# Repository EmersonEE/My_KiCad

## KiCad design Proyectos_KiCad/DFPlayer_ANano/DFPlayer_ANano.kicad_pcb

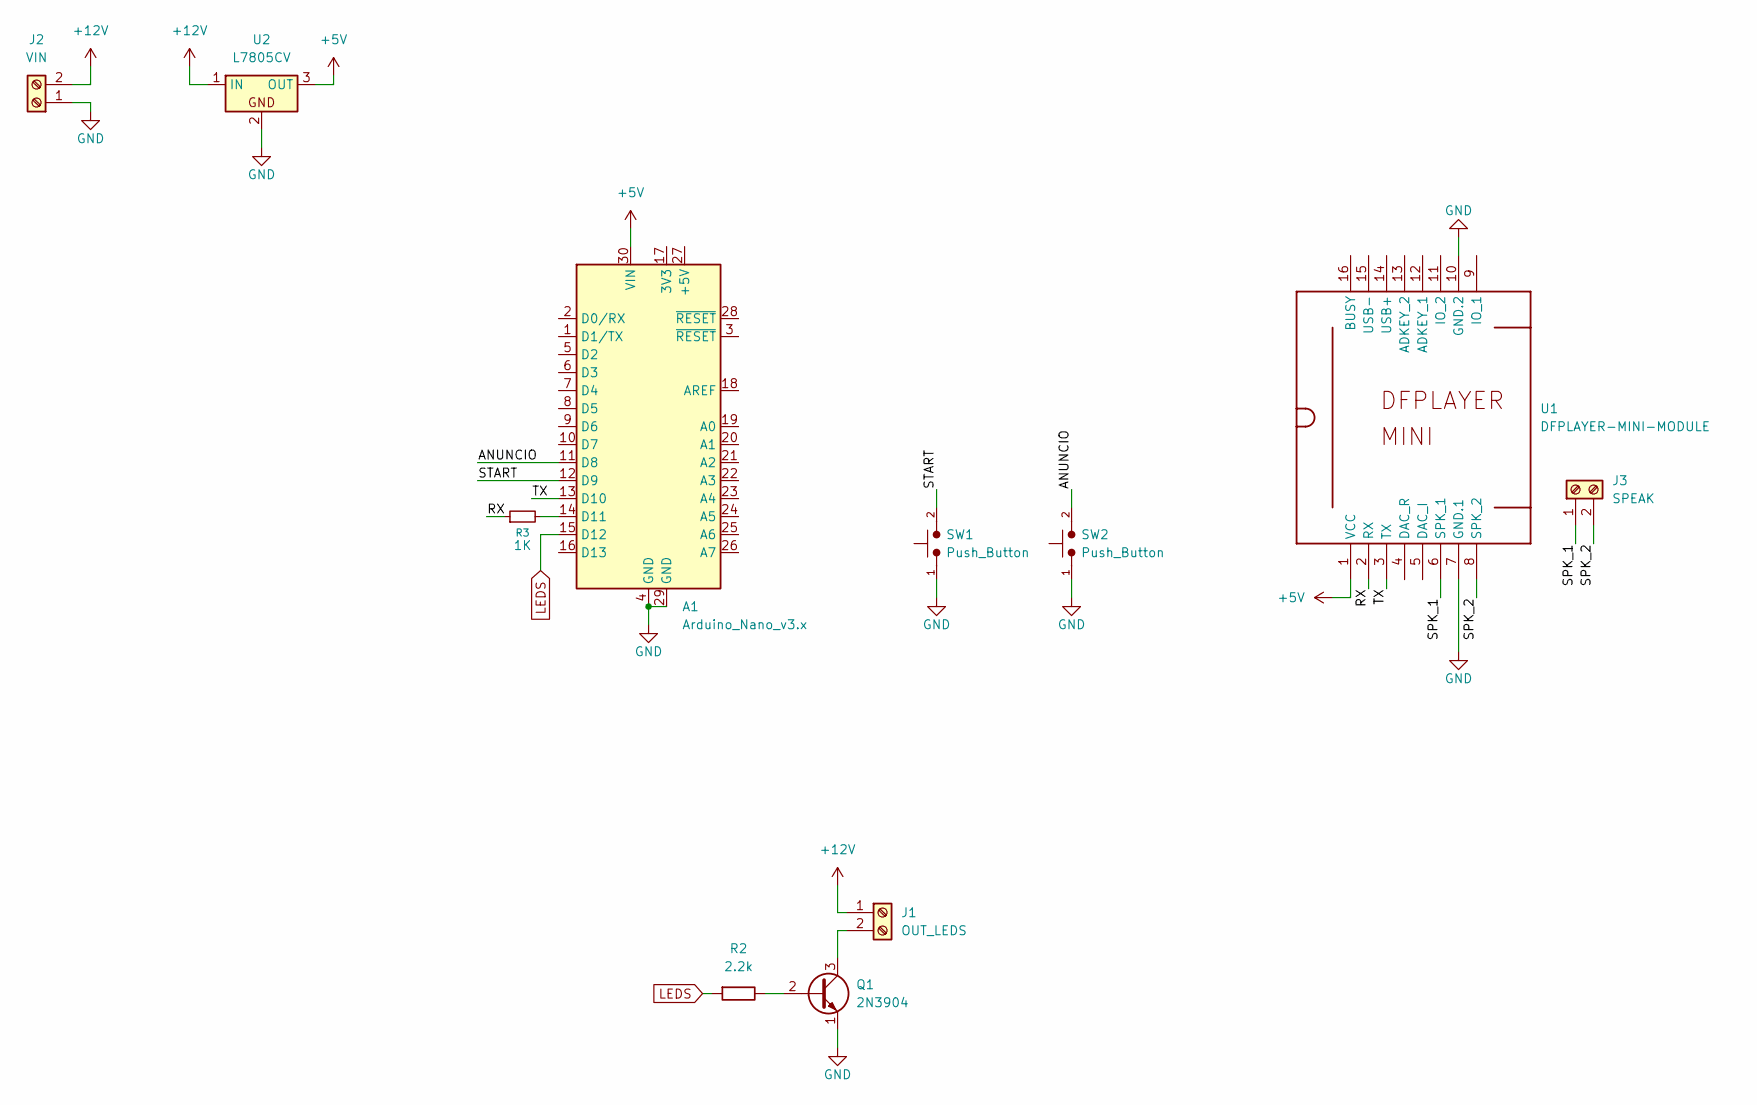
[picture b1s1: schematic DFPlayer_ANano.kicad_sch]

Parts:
A1: Arduino_Nano_v3.x; Arduino_Nano
J1: OUT_LEDS; TerminalBlock_Phoenix_MKDS-1,5-2-5.08_1x02_P5.08mm_Horizont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
J2: VIN; TerminalBlock_Phoenix_MKDS-1,5-2-5.08_1x02_P5.08mm_Horizont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
J3: SPEAK; TerminalBlock_Phoenix_MKDS-1,5-2-5.08_1x02_P5.08mm_Horizont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
Q1: 2N3904; TO-92L_Inline_Wide
R2: 2.2k; R_Axial_DIN0207_L6.3mm_D2.5mm_P10.16mm_Horizontal
R3: 1K; R_Axial_DIN0204_L3.6mm_D1.6mm_P10.16mm_Horizontal
SW1, SW2: Push_Button; SW_PUSH_6mm
U1: DFPLAYER-MINI-MODULE
U2: L7805CV; TO-220-3_Vertical

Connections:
+5V: A1.30 (VIN), U1.1 (VCC), U2.3 (OUT)
+12V: J1.1, J2.2, U2.1 (IN)
/ANUNCIO: A1.11 (D8), SW2.2
/RX: R3.1, U1.2 (RX)
/SPK_1: J3.1, U1.6 (SPK_1)
/SPK_2: J3.2, U1.8 (SPK_2)
/START: A1.12 (D9), SW1.2
/TX: A1.13 (D10), U1.3 (TX)
GND: A1.4 (GND), A1.29 (GND), J2.1, Q1.1 (E), SW1.1, SW2.1, U1.7 (GND.1), U1.10 (GND.2), U2.2
LEDS: A1.15 (D12), R2.1
unnamed: A1.14 (D11), R3.2
unnamed: J1.2, Q1.3 (C)
unnamed: Q1.2 (B), R2.2

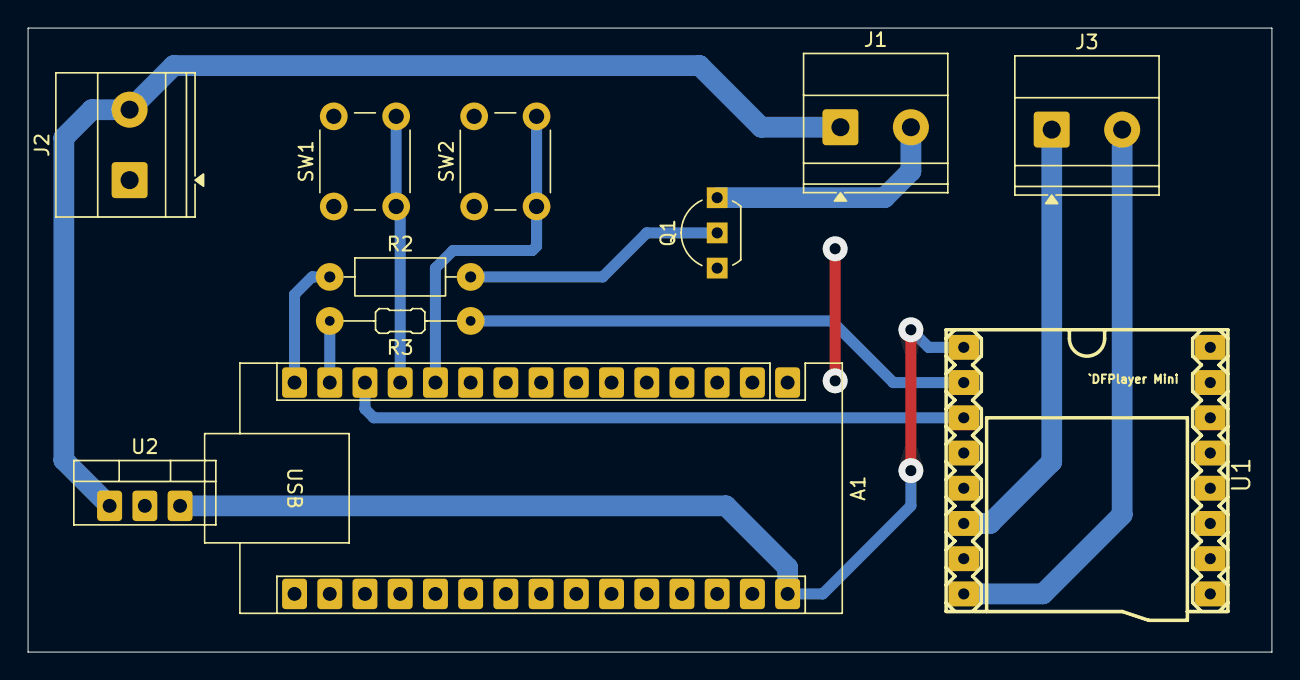
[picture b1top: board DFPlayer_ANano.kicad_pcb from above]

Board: 2 copper layers, 89.7 x 45.0 mm, 11 parts (0 on the bottom side), 13 nets.

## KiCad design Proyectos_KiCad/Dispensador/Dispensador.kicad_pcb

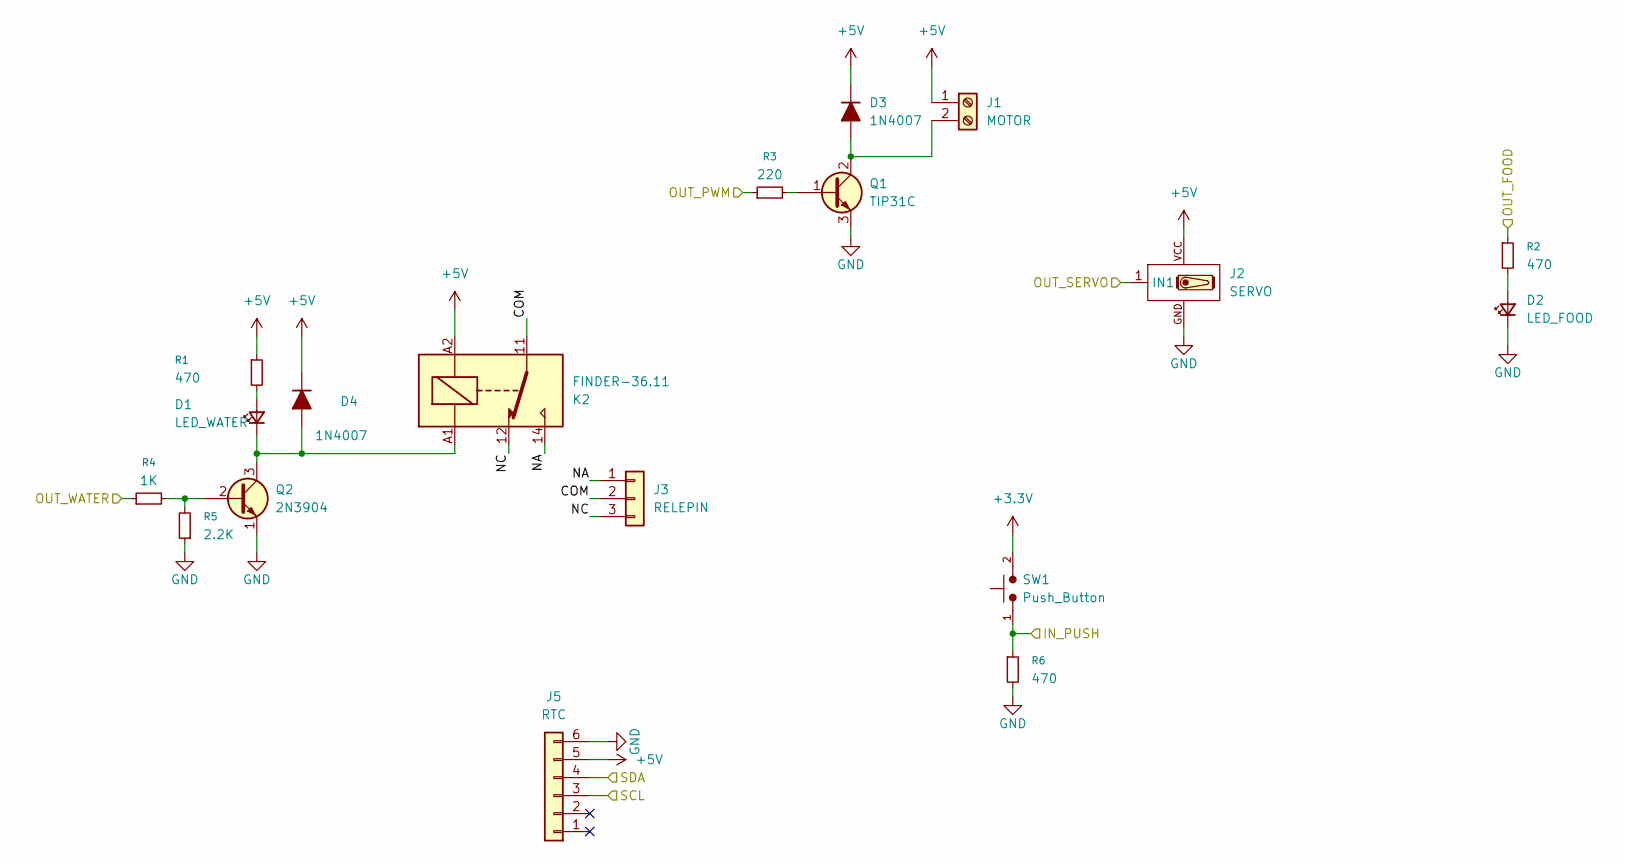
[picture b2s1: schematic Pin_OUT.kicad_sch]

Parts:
D1: LED_WATER; LED_D5.0mm
D2: LED_FOOD; LED_D5.0mm
D3, D4: 1N4007; D_DO-41_SOD81_P7.62mm_Horizontal
J1: MOTOR; TerminalBlock_Phoenix_MKDS-1,5-2-5.08_1x02_P5.08mm_Horizont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
J2: SERVO; ServoPort_01_Vertical
J3: RELEPIN; TerminalBlock_Phoenix_MKDS-1,5-3-5.08_1x03_P5.08mm_Horizont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
J5: RTC; PinSocket_1x06_P2.54mm_Vertical
K2: FINDER-36.11; Relay_SPDT_Finder_36.11
Q1: TIP31C; TO-220-3_Vertical_BCE
Q2: 2N3904; TO-92_Inline_Wide_EBC
R1, R2, R6: 470
R3: 220
R4: 1K
R5: 2.2K
SW1: Push_Button; SW_PUSH_6mm

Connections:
+3.3V: SW1.2; also elsewhere on the board
+5V: D3.1 (K), D4.1 (K), J1.1, J2.VCC, J5.5, K2.A2, R1.1; also elsewhere on the board
/ESP32/IN_PUSH: R6.1, SW1.1; also elsewhere on the board
/ESP32/OUT_FOOD: R2.1; also elsewhere on the board
/ESP32/OUT_PWM: R3.1; also elsewhere on the board
/ESP32/OUT_SERVO: J2.1 (IN1); also elsewhere on the board
/ESP32/OUT_WATER: R4.1; also elsewhere on the board
/ESP32/SCL: J5.3; also elsewhere on the board
/ESP32/SDA: J5.4; also elsewhere on the board
/Pin_OUT/COM: J3.2, K2.11
/Pin_OUT/NA: J3.1, K2.14
/Pin_OUT/NC: J3.3, K2.12
GND: D2.1 (K), J2.GND, J5.6, Q1.3 (E), Q2.1 (E), R5.1, R6.2; also elsewhere on the board
unnamed: D1.2 (A), R1.2
unnamed: D1.1 (K), D4.2 (A), K2.A1, Q2.3 (C)
unnamed: D2.2 (A), R2.2
unnamed: D3.2 (A), J1.2, Q1.2 (C)
unnamed: Q1.1 (B), R3.2
unnamed: Q2.2 (B), R4.2, R5.2

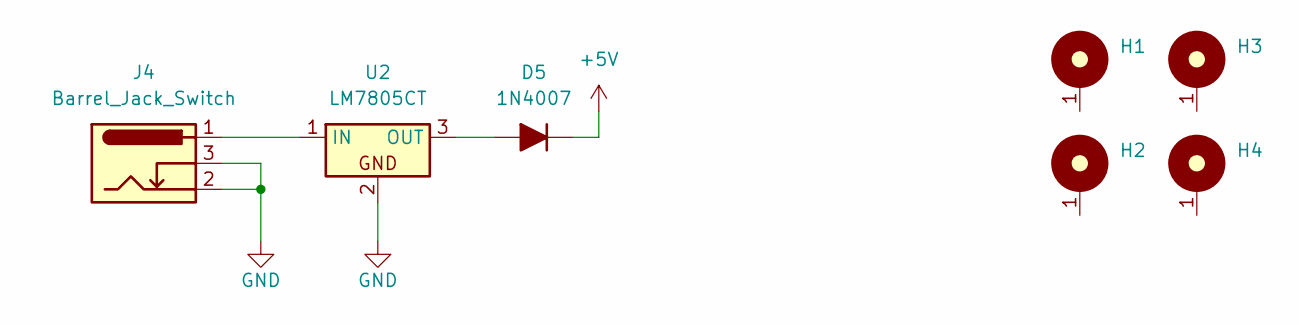
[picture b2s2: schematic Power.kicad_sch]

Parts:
D5: 1N4007; D_DO-41_SOD81_P7.62mm_Horizontal
H1, H2, H3, H4: MountingHole_3.2mm_M3_ISO14580
J4: Barrel_Jack_Switch; BarrelJack_Horizontal
U2: LM7805CT; TO-220-3_Vertical

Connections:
+5V: D5.1 (K); also elsewhere on the board
GND: J4.2, J4.3, U2.2; also elsewhere on the board
unnamed: D5.2 (A), U2.3 (OUT)
unnamed: J4.1, U2.1 (IN)

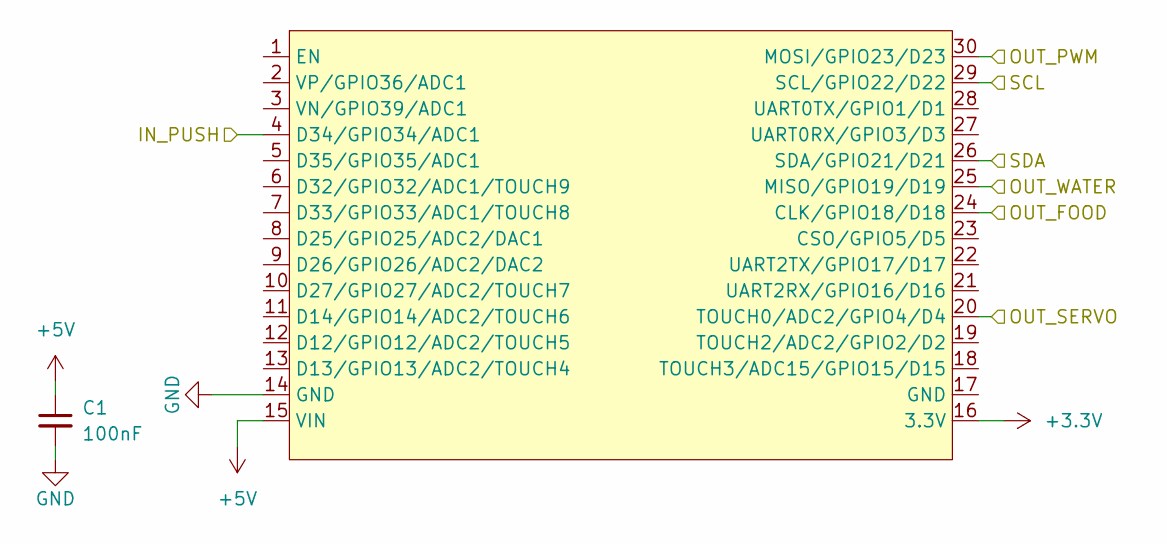
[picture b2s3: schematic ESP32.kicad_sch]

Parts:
C1: 100nF; C_Disc_D4.3mm_W1.9mm_P5.00mm
U1: ESP32_DevKit_V1_DOIT; ESP32_DEVKIT_V1_E32

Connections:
+3.3V: U1.16 (3.3V); also elsewhere on the board
+5V: C1.1, U1.15 (VIN); also elsewhere on the board
/ESP32/IN_PUSH: U1.4 (D34/GPIO34/ADC1); also elsewhere on the board
/ESP32/OUT_FOOD: U1.24 (CLK/GPIO18/D18); also elsewhere on the board
/ESP32/OUT_PWM: U1.30 (MOSI/GPIO23/D23); also elsewhere on the board
/ESP32/OUT_SERVO: U1.20 (TOUCH0/ADC2/GPIO4/D4); also elsewhere on the board
/ESP32/OUT_WATER: U1.25 (MISO/GPIO19/D19); also elsewhere on the board
/ESP32/SCL: U1.29 (SCL/GPIO22/D22); also elsewhere on the board
/ESP32/SDA: U1.26 (SDA/GPIO21/D21); also elsewhere on the board
GND: C1.2, U1.14 (GND); also elsewhere on the board

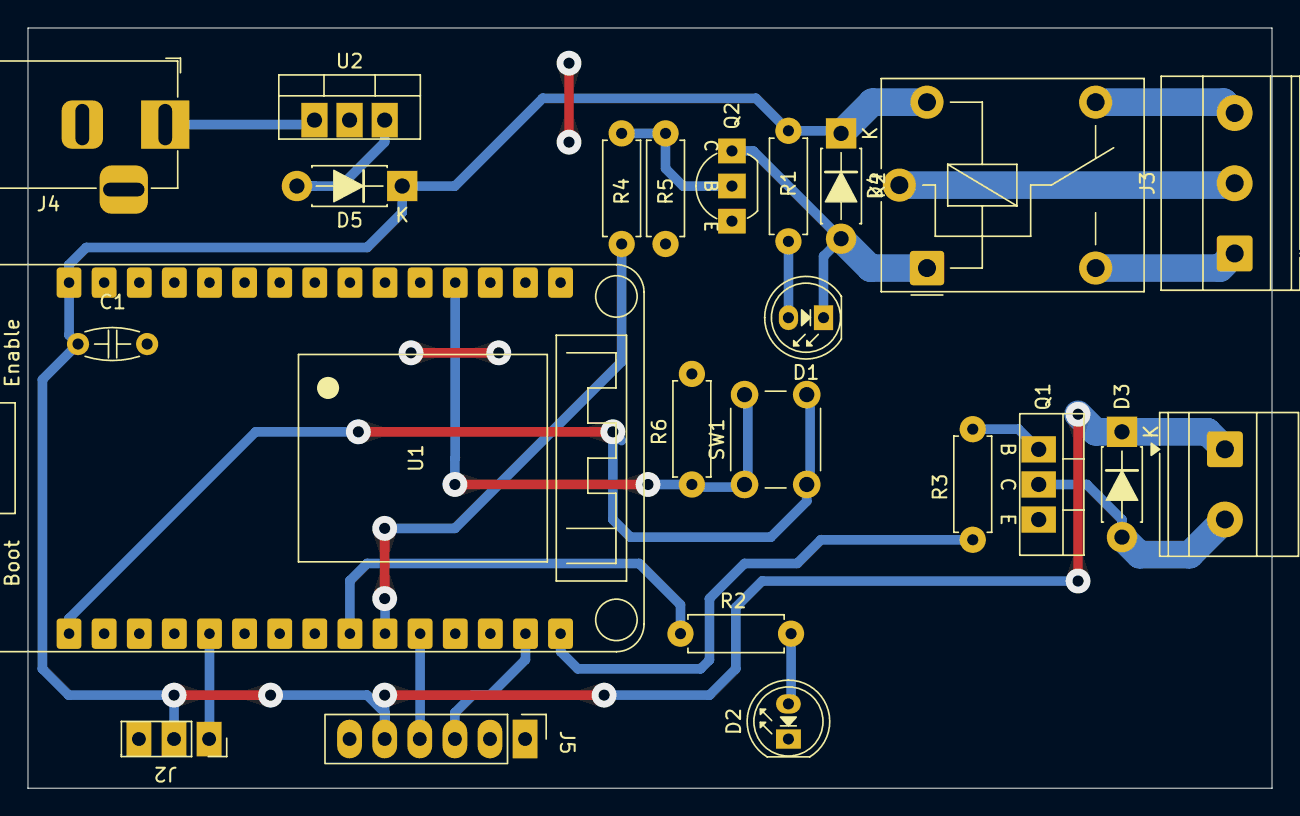
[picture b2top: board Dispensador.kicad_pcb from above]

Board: 2 copper layers, 90.0 x 55.0 mm, 27 parts (0 on the bottom side), 21 nets.

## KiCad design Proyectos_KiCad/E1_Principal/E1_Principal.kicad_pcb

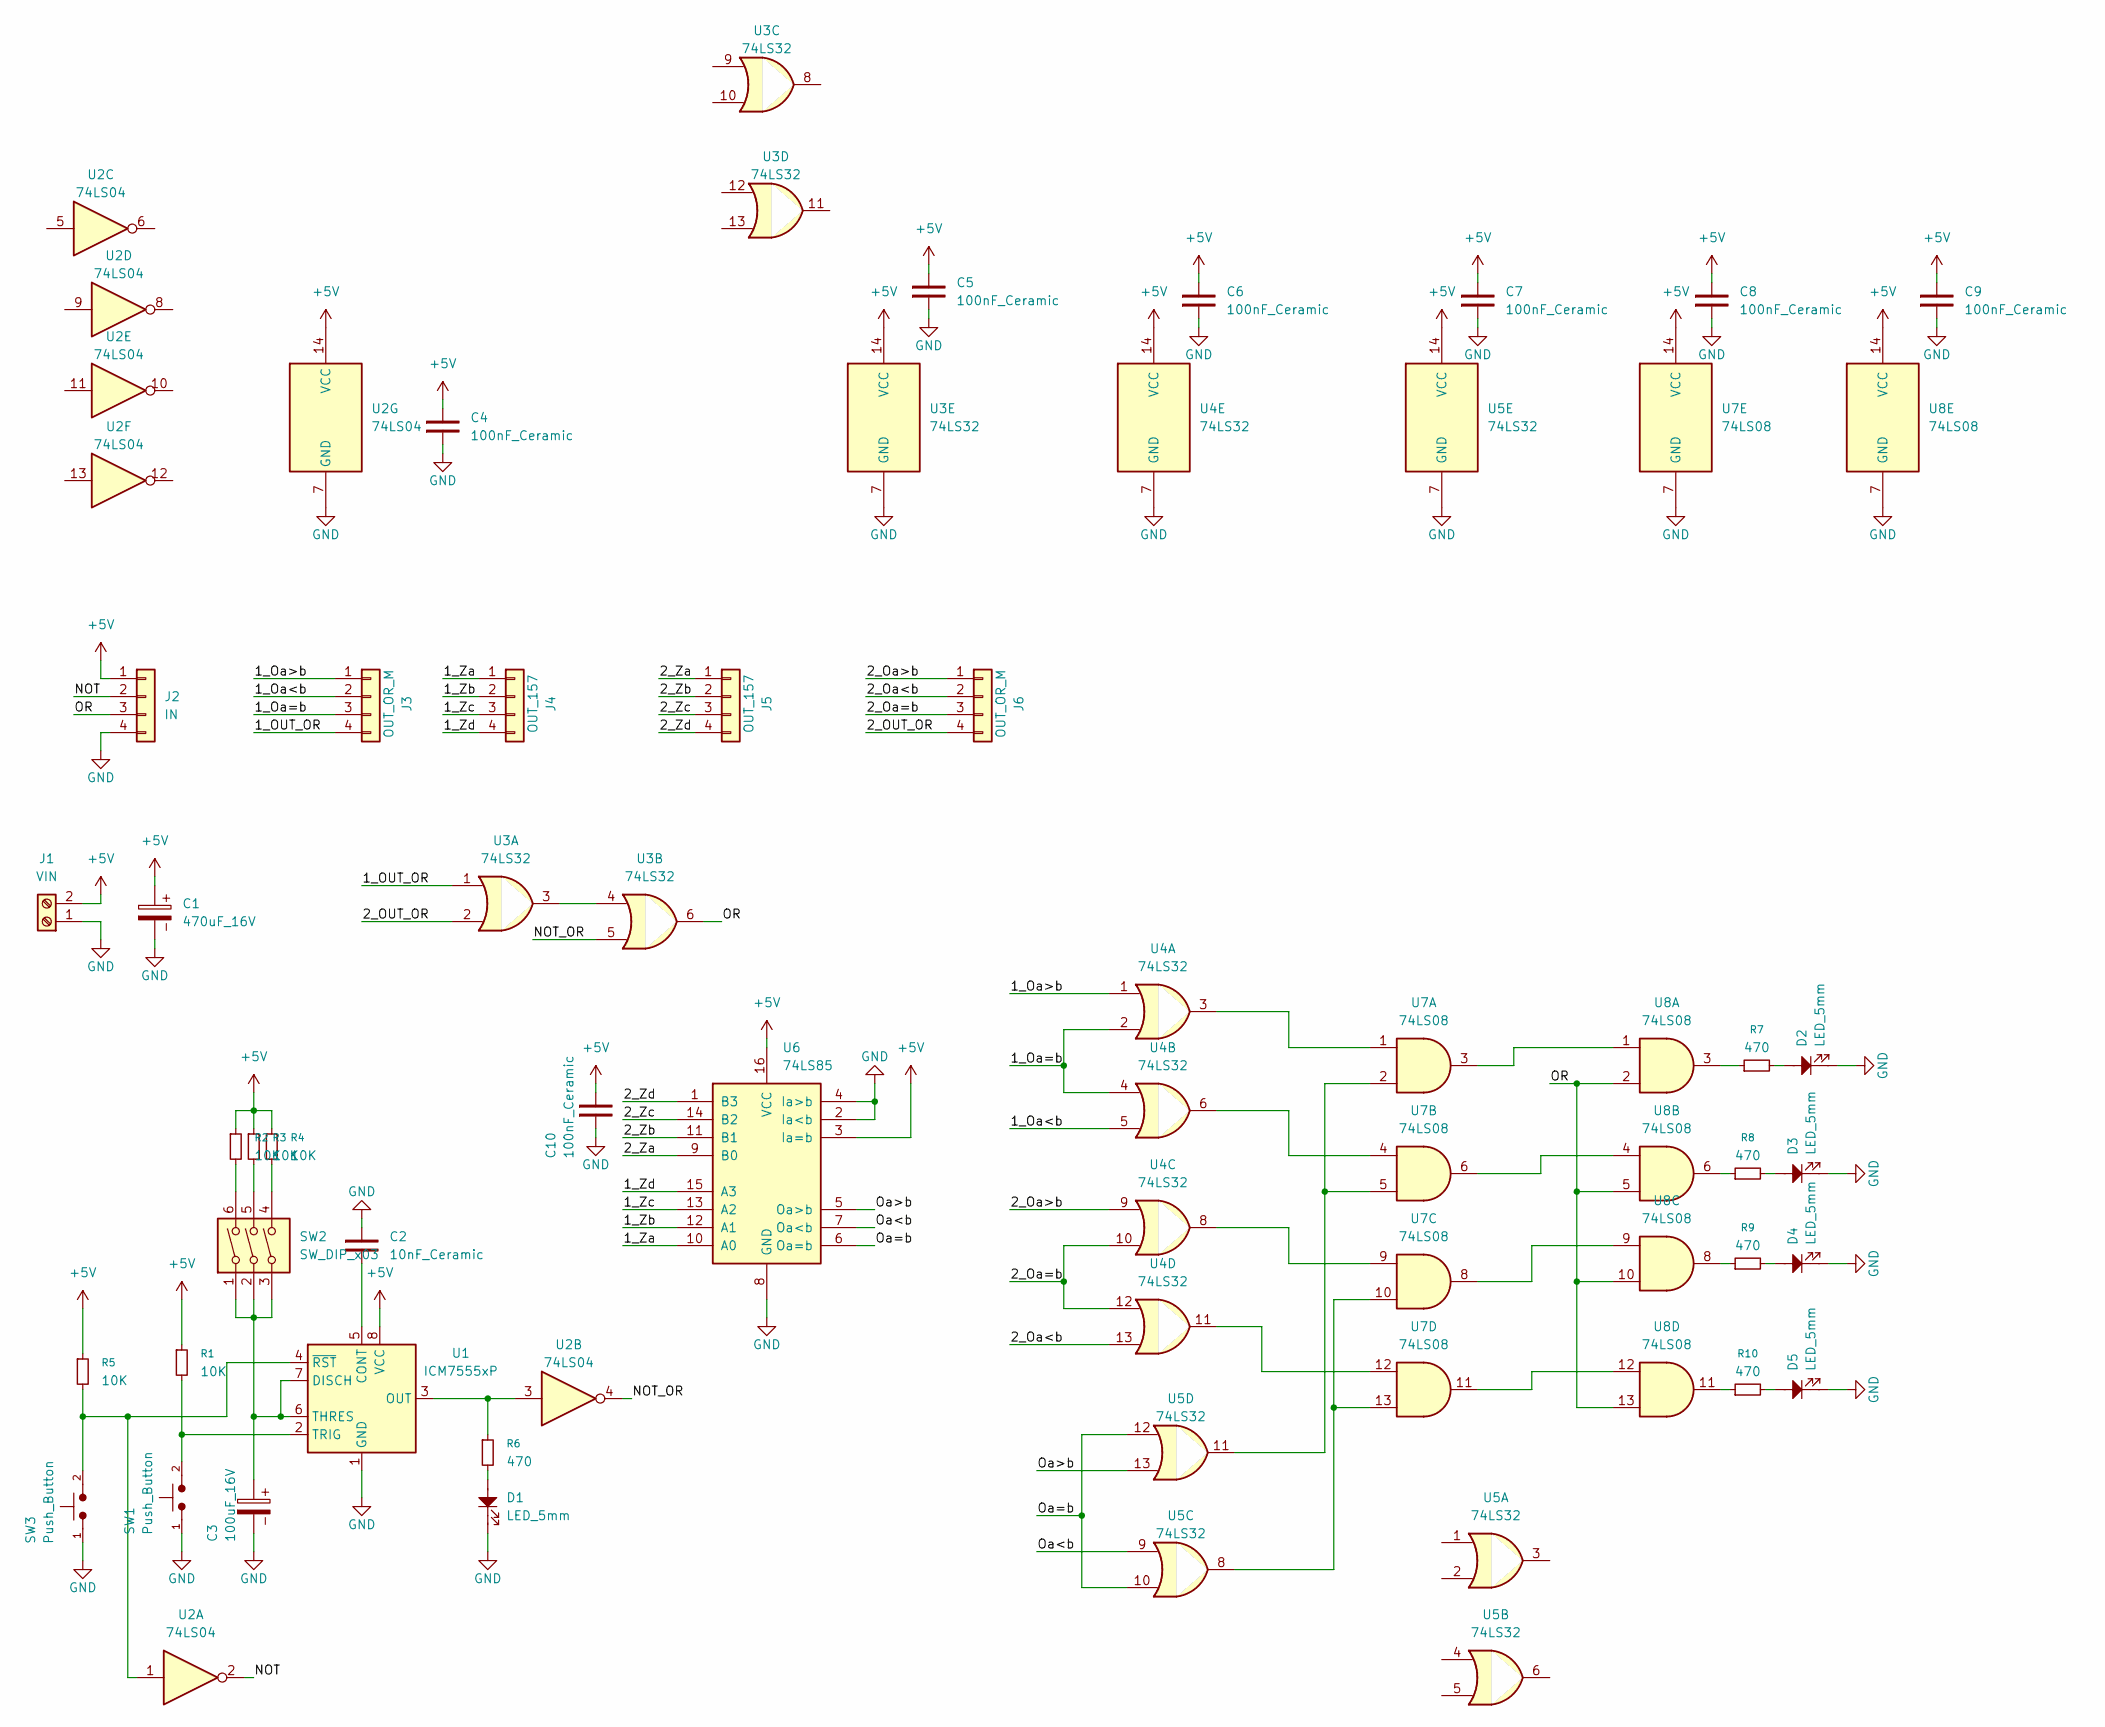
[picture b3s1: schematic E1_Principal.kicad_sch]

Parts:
C1: 470uF_16V; CP_Radial_D8.0mm_P3.50mm
C2: 10nF_Ceramic; C_Disc_D5.0mm_W2.5mm_P2.50mm
C3: 100uF_16V; CP_Radial_D5.0mm_P2.00mm
C4, C5, C6, C7, C8, C9, C10: 100nF_Ceramic; C_0805_2012Metric_Pad1.15x1.40mm
D1, D2, D3, D4, D5: LED_5mm; LED_D5.0mm
J1: VIN; TerminalBlock_Phoenix_MKDS-1,5-2-5.08_1x02_P5.08mm_Horizont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
J2: IN; PinHeader_1x04_P2.54mm_Vertical
J3, J6: OUT_OR_M; PinHeader_1x04_P2.54mm_Vertical
J4, J5: OUT_157; PinHeader_1x04_P2.54mm_Vertical
R1, R2, R3, R4, R5: 10K
R6, R7, R8, R9, R10: 470
SW1, SW3: Push_Button; SW_PUSH_6mm
SW2: SW_DIP_x03; SW_DIP_SPSTx03_Slide_9.78x9.8mm_W7.62mm_P2.54mm
U1: ICM7555xP; DIP-8_W7.62mm_LongPads
U2: 74LS04; DIP-14_W7.62mm_LongPads
U3, U4, U5: 74LS32; DIP-14_W7.62mm_LongPads
U6: 74LS85; DIP-16_W7.62mm_LongPads
U7, U8: 74LS08; DIP-14_W7.62mm_LongPads

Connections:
+5V: C1.1, C4.2, C5.2, C6.2, C7.2, C8.2, C9.2, C10.2, J1.2, J2.1, R1.1, R2.1, R3.1, R4.1, R5.1, U1.8 (VCC), U2.14 (VCC), U3.14 (VCC), U4.14 (VCC), U5.14 (VCC), U6.3 (Ia=b), U6.16 (VCC), U7.14 (VCC), U8.14 (VCC)
/1_OUT_OR: J3.4, U3.1
/1_Oa<b: J3.2, U4.5
/1_Oa=b: J3.3, U4.2, U4.4
/1_Oa>b: J3.1, U4.1
/1_Za: J4.1, U6.10 (A0)
/1_Zb: J4.2, U6.12 (A1)
/1_Zc: J4.3, U6.13 (A2)
/1_Zd: J4.4, U6.15 (A3)
/2_OUT_OR: J6.4, U3.2
/2_Oa<b: J6.2, U4.13
/2_Oa=b: J6.3, U4.10, U4.12
/2_Oa>b: J6.1, U4.9
/2_Za: J5.1, U6.9 (B0)
/2_Zb: J5.2, U6.11 (B1)
/2_Zc: J5.3, U6.14 (B2)
/2_Zd: J5.4, U6.1 (B3)
/NOT: J2.2, U2.2
/NOT_OR: U2.4, U3.5
/OR: J2.3, U3.6, U8.2, U8.5, U8.10, U8.13
/Oa<b: U5.9, U6.7 (Oa<b)
/Oa=b: U5.10, U5.12, U6.6 (Oa=b)
/Oa>b: U5.13, U6.5 (Oa>b)
GND: C1.2, C2.2, C3.2, C4.1, C5.1, C6.1, C7.1, C8.1, C9.1, C10.1, D1.1, D2.1, D3.1, D4.1, D5.1, J1.1, J2.4, SW1.1, SW3.1, U1.1 (GND), U2.7 (GND), U3.7 (GND), U4.7 (GND), U5.7 (GND), U6.2 (Ia<b), U6.4 (Ia>b), U6.8 (GND), U7.7 (GND), U8.7 (GND)
unnamed: D1.2, R6.2
unnamed: D2.2, R7.2
unnamed: D3.2, R8.2
unnamed: D4.2, R9.2
unnamed: D5.2, R10.2
unnamed: R2.2, SW2.6
unnamed: R3.2, SW2.5
unnamed: R4.2, SW2.4
unnamed: R7.1, U8.3
unnamed: R8.1, U8.6
unnamed: R9.1, U8.8
unnamed: R10.1, U8.11
unnamed: C2.1, U1.5 (CONT)
unnamed: C3.1, SW2.1, SW2.2, SW2.3, U1.6 (THRES), U1.7 (DISCH)
unnamed: R6.1, U1.3 (OUT), U2.3
unnamed: R1.2, SW1.2, U1.2 (TRIG)
unnamed: R5.2, SW3.2, U1.4 (~RST), U2.1
unnamed: U3.3, U3.4
unnamed: U4.3, U7.1
unnamed: U4.6, U7.4
unnamed: U4.8, U7.9
unnamed: U4.11, U7.12
unnamed: U5.8, U7.10, U7.13
unnamed: U5.11, U7.2, U7.5
unnamed: U7.3, U8.1
unnamed: U7.6, U8.4
unnamed: U7.8, U8.9
unnamed: U7.11, U8.12

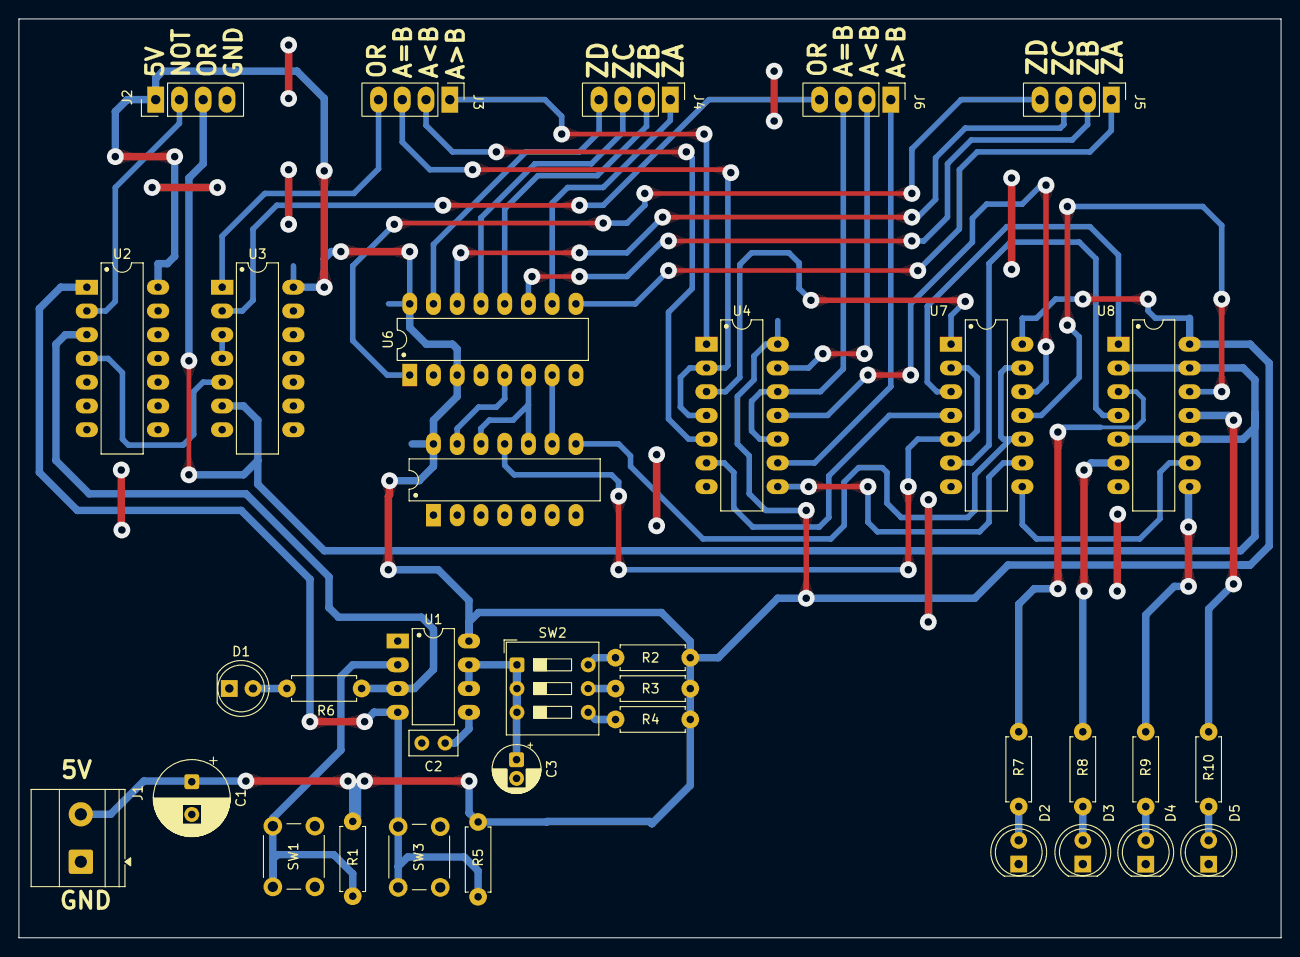
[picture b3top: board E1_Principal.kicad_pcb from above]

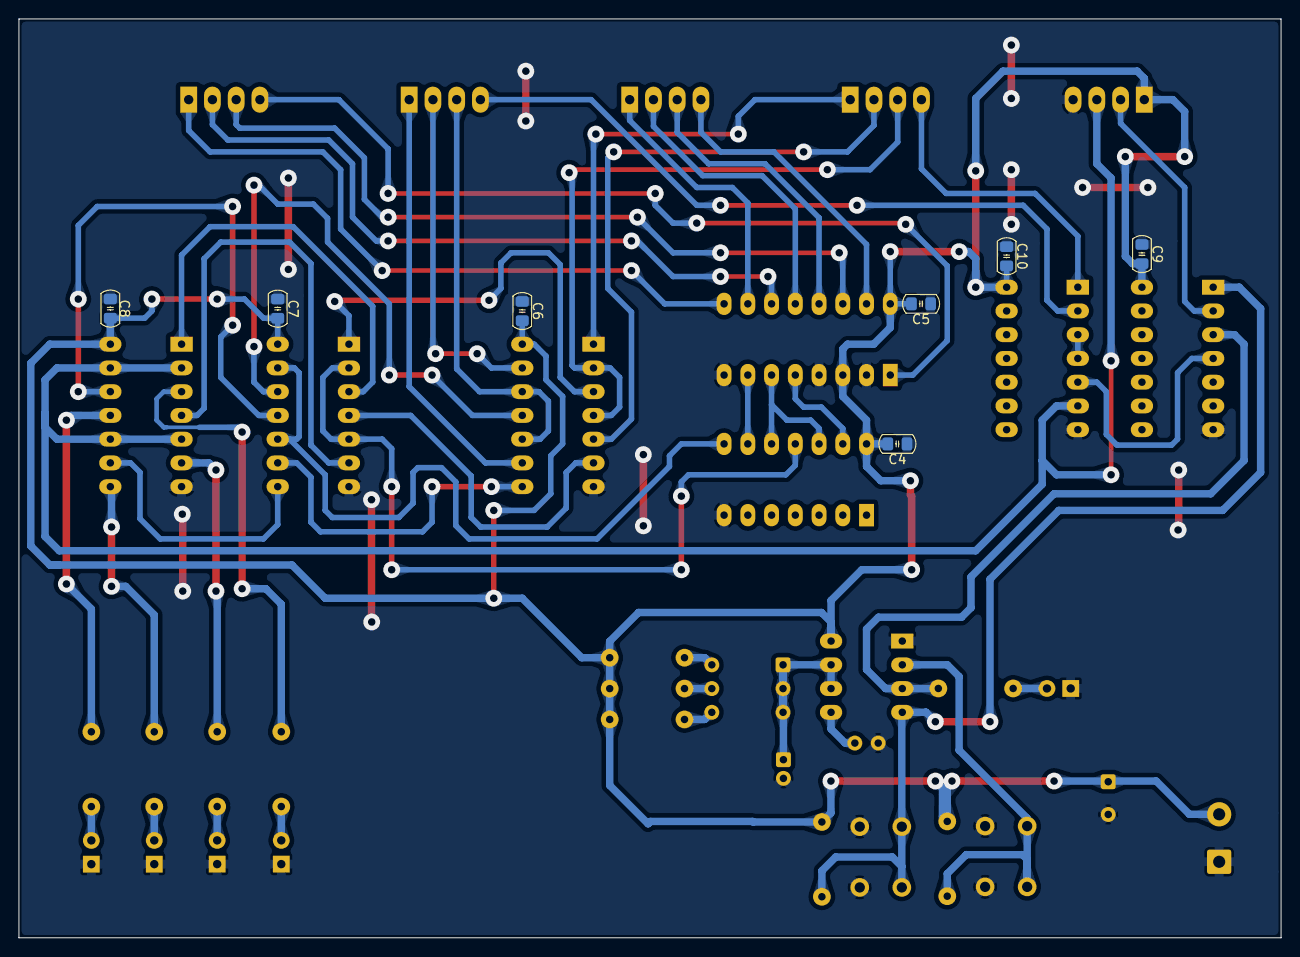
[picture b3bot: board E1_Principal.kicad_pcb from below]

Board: 2 copper layers, 135.0 x 98.3 mm, 42 parts (7 on the bottom side), 52 nets.

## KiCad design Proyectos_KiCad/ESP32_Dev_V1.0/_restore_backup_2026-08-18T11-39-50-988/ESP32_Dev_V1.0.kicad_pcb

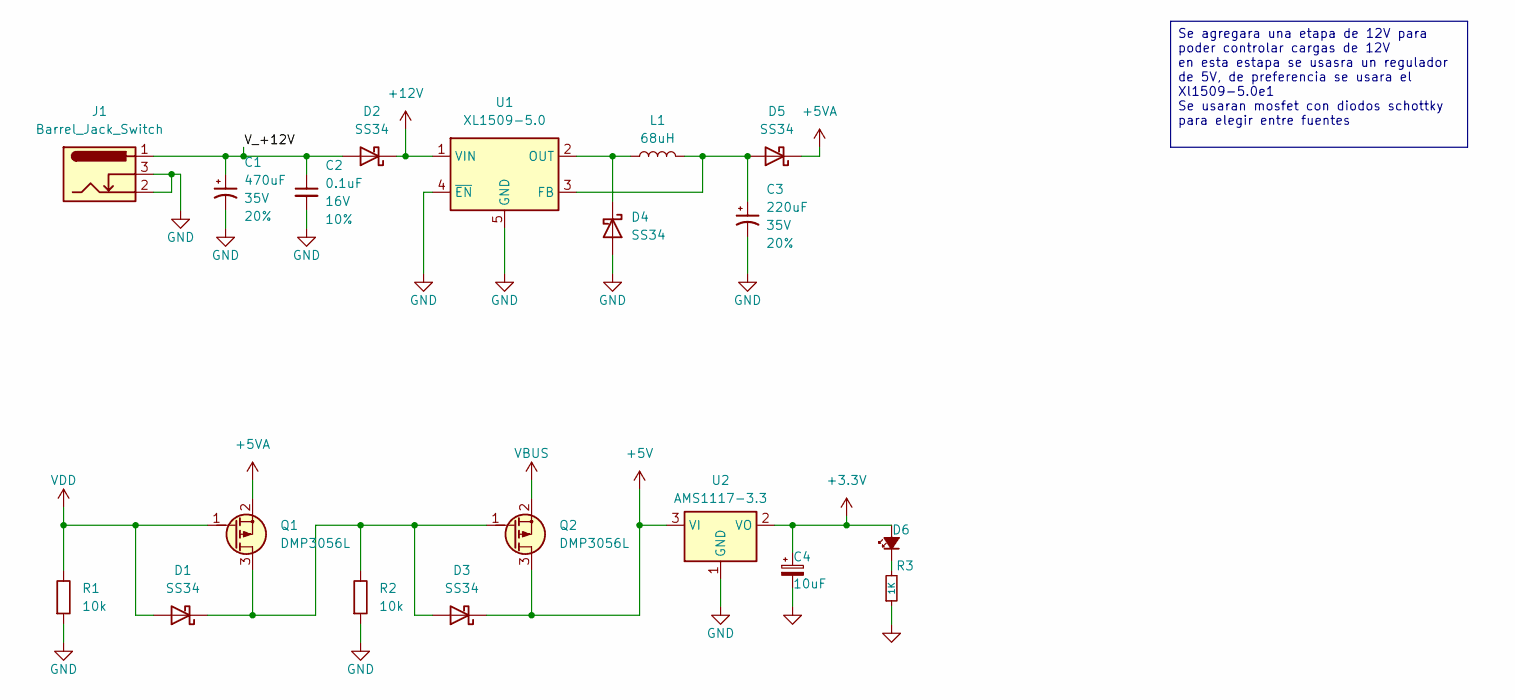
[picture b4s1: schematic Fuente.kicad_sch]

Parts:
C1: 470uF; Electrolytic_10.3x10.3mm; Voltage 35V; Tolerance 20%
C2: 0.1uF; C_0805_2012Metric; Voltage 16V; Tolerance 10%
C3: 220uF; Electrolytic_10.3x10.3mm; Voltage 35V; Tolerance 20%
C4: 10uF; CP_Elec_5x5.3; PartNo 865080642006
D1, D2, D3, D4, D5: SS34; D_SMA
D6: LED; LED_0805_2012Metric; PartNo 150060RS75000
J1: Barrel_Jack_Switch; BarrelJack_GCT_DCJ200-10-A_Horizontal
L1: 68uH; L_AVX_LMLP07A7
Q1, Q2: DMP3056L; SOT-23
R1, R2: 10k; R_0805_2012Metric
R3: 1K; R_0805_2012Metric; PartNo RC0805FR-071KL
U1: XL1509-5.0; SOIC-8_3.9x4.9mm_P1.27mm
U2: AMS1117-3.3; SOT-223-3_TabPin2

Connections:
+3.3V: C4.1, D6.2 (A), U2.2 (VO); also elsewhere on the board
+5V: D3.1 (K), Q2.3 (D), U2.3 (VI); also elsewhere on the board
+5VA: D5.1 (K), Q1.2 (S)
+12V: D2.1 (K), U1.1 (VIN); also elsewhere on the board
/Fuente/V_+12V: C1.1, C2.1, D2.2 (A), J1.1
GND: C1.2, C2.2, C3.2, C4.2, D4.2 (A), J1.2, J1.3, R1.1, R2.1, R3.1, U1.4 (~EN), U1.5 (GND), U1.6 (GND), U1.7 (GND), U1.8 (GND), U2.1 (GND); also elsewhere on the board
unnamed: D1.1 (K), D3.2 (A), Q1.3 (D), Q2.1 (G), R2.2
unnamed: D4.1 (K), L1.1, U1.2 (OUT)
unnamed: C3.1, D5.2 (A), L1.2, U1.3 (FB)
unnamed: D6.1 (K), R3.2
VBUS: Q2.2 (S); also elsewhere on the board
VDD: D1.2 (A), Q1.1 (G), R1.2; also elsewhere on the board

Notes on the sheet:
Se agregara una etapa de 12V para poder controlar cargas de 12V en esta estapa se usasra un regulador de 5V, de preferencia se usara el Xl1509-5.0e1 Se usaran mosfet con diodos schottky para elegir entre fuentes

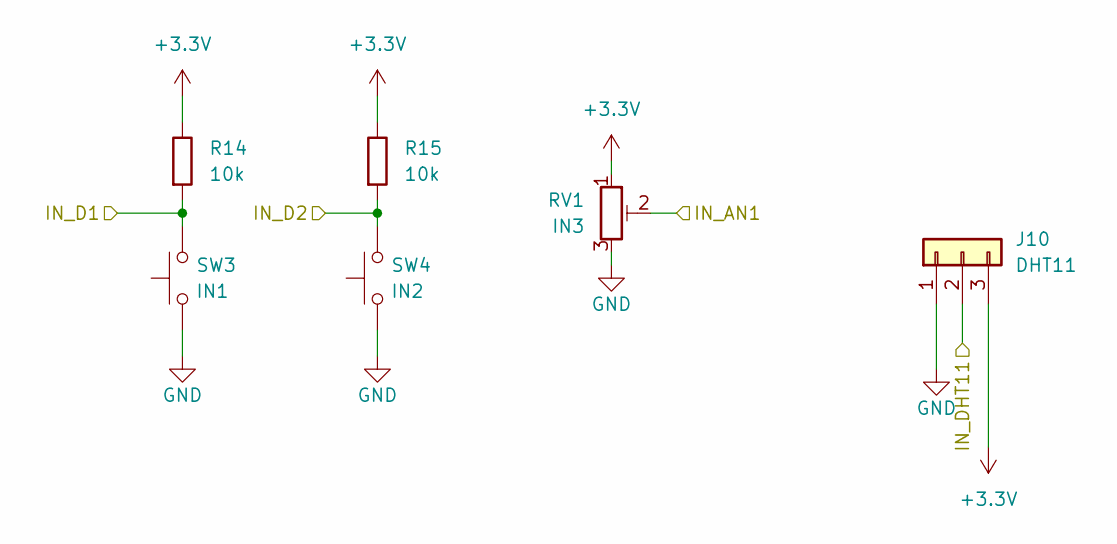
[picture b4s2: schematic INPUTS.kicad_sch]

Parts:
J10: DHT11; PinSocket_1x03_P2.54mm_Vertical
R14, R15: 10k; R_0805_2012Metric
RV1: IN3; Potentiometer_Bourns_3266Y_Vertical
SW3: IN1; Push_SMD_6x3.5mm; Mfg Part# 8-004 SMD Button 8x3.6mm Height=2.5mm
SW4: IN2; Push_SMD_6x3.5mm; Mfg Part# 8-004 SMD Button 8x3.6mm Height=2.5mm

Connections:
+3.3V: J10.3, R14.2, R15.2, RV1.1; also elsewhere on the board
/INPUTS/IN_AN1: RV1.2; also elsewhere on the board
/INPUTS/IN_D1: R14.1, SW3.2; also elsewhere on the board
/INPUTS/IN_D2: R15.1, SW4.2; also elsewhere on the board
/INPUTS/IN_DHT11: J10.2; also elsewhere on the board
GND: J10.1, RV1.3, SW3.1, SW4.1; also elsewhere on the board
